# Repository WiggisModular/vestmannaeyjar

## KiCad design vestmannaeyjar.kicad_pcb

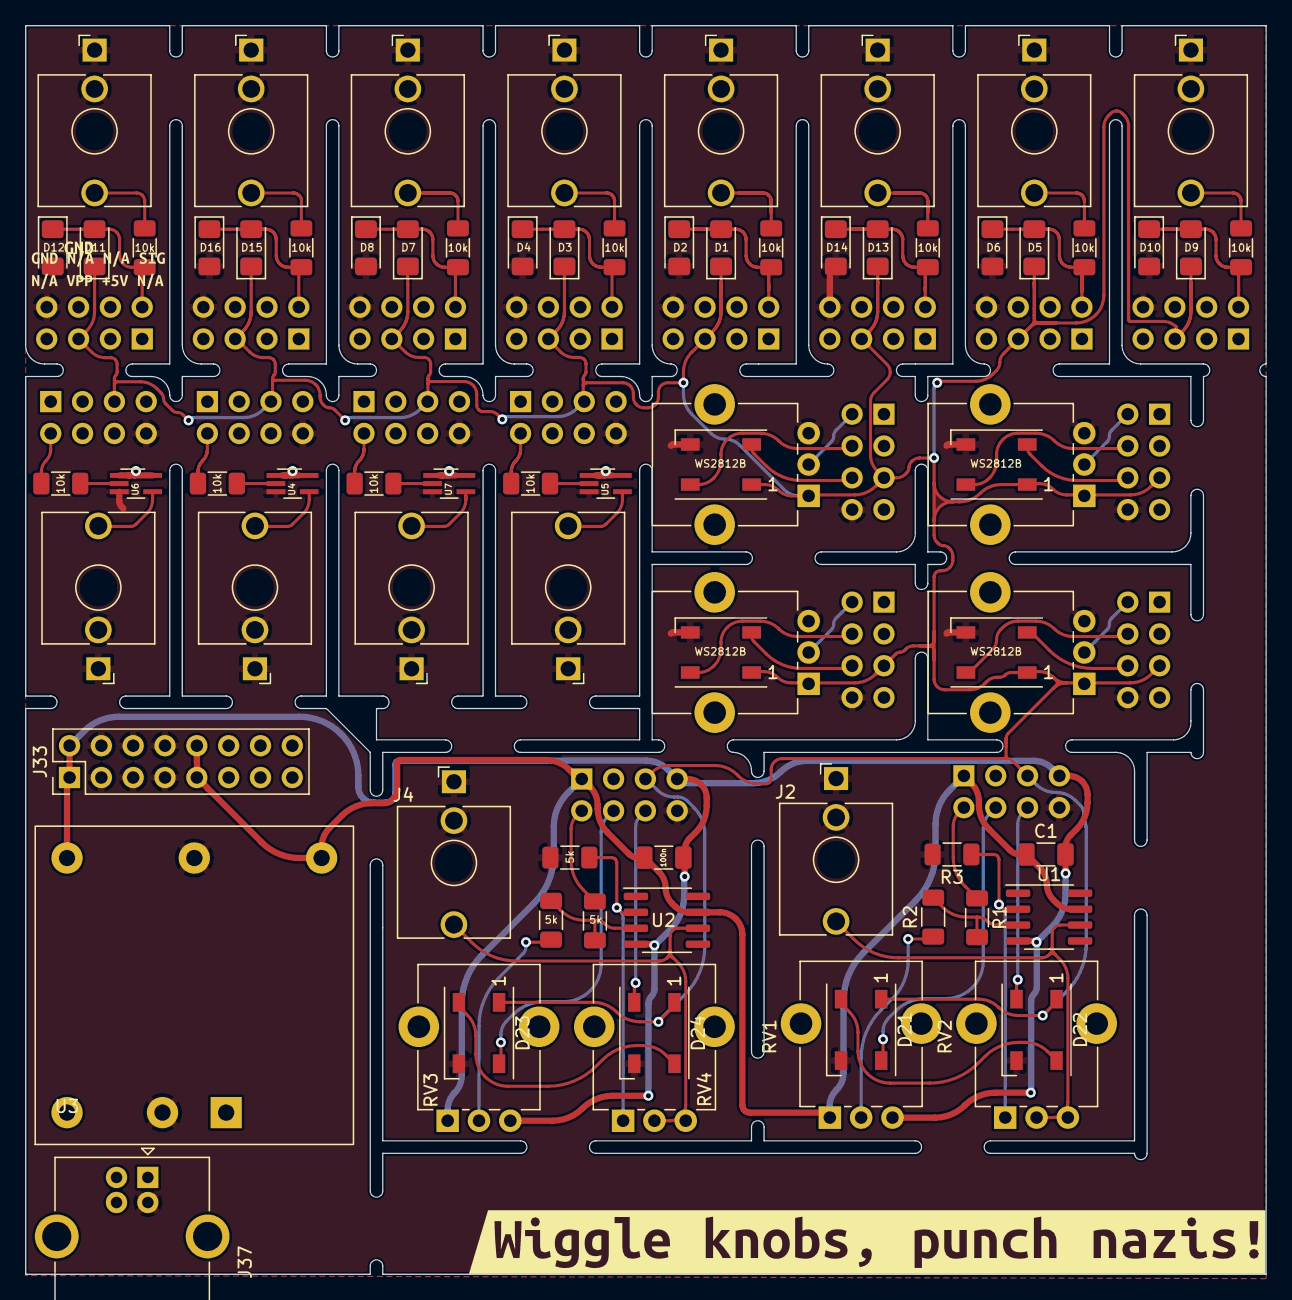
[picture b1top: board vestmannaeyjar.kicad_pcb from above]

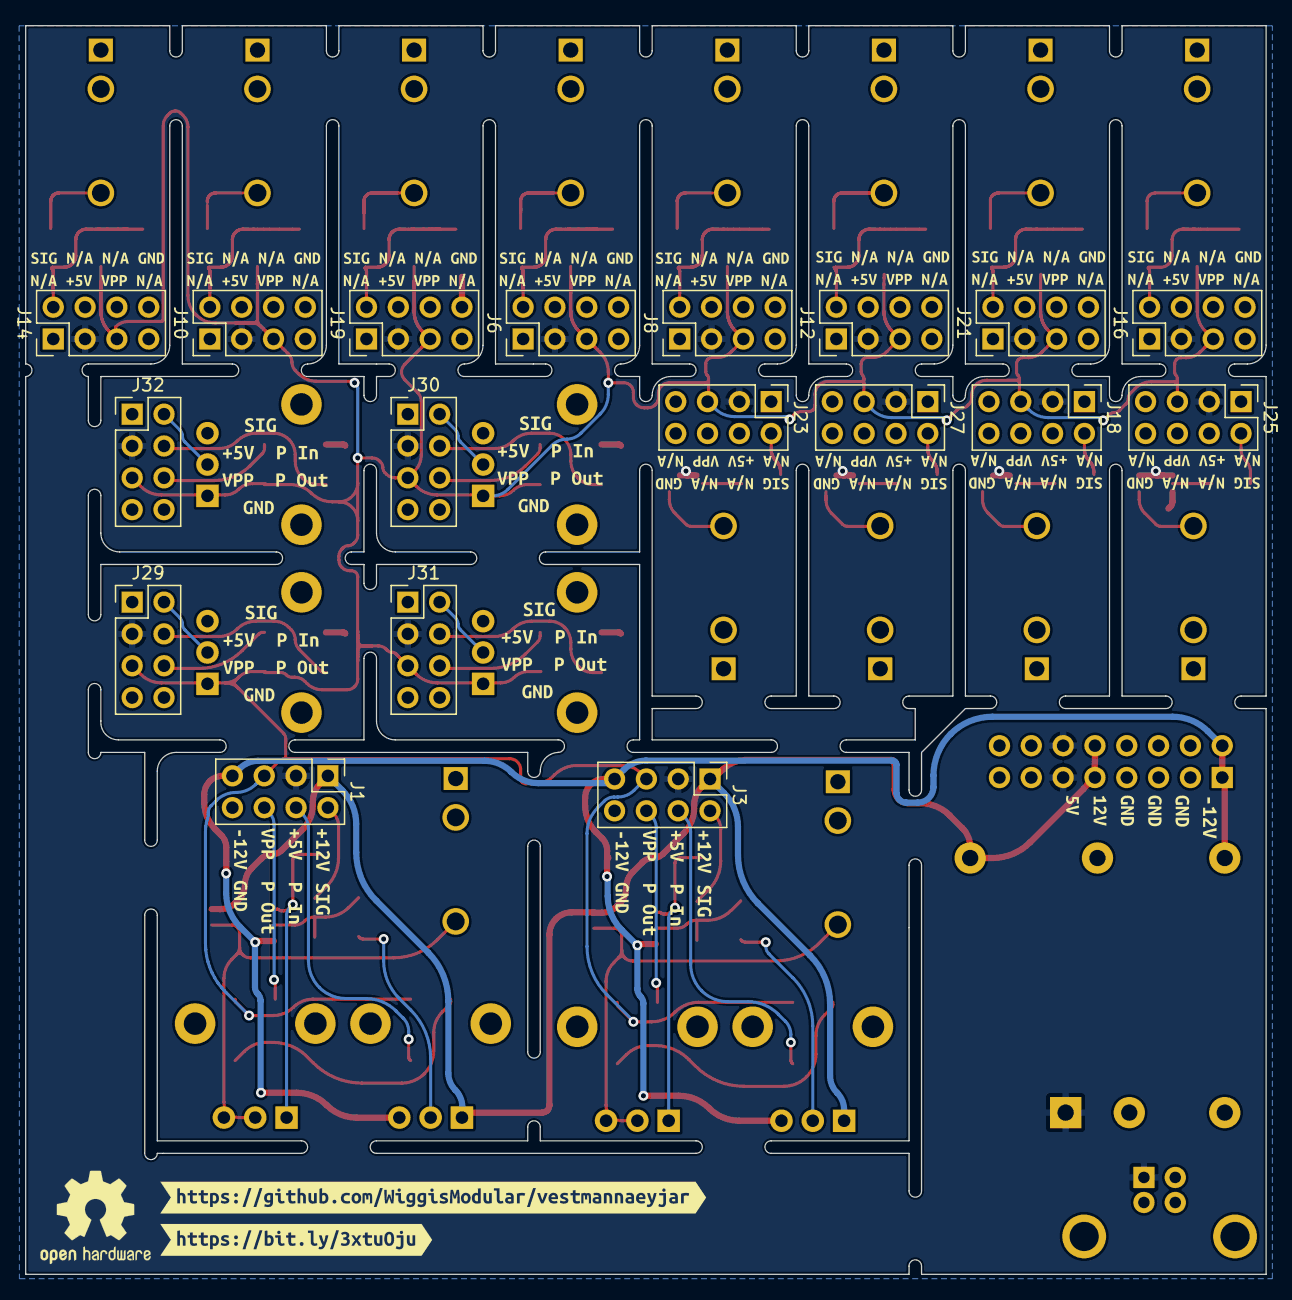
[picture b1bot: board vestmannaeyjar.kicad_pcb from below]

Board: 2 copper layers, 99.0 x 99.7 mm, 117 parts (39 on the bottom side), 61 nets.

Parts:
C1, C2: 100n; C_1206_3216Metric_Pad1.33x1.80mm_HandSolder
D1, D2, D3, D4, D5, D6, D7, D8, D9, D10, D11, D12, D13, D14, D15, D16: D; D_1206_3216Metric_Pad1.42x1.75mm_HandSolder
D17, D18, D19, D20, D21, D22, D23, D24: WS2812B; LED_WS2812B_PLCC4_5.0x5.0mm_P3.2mm
J1, J3, J6, J8, J10, J12, J14, J16, J18, J19, J21, J23, J25, J27, J29, J30, J31, J32: Conn_02x04_Odd_Even; PinHeader_2x04_P2.54mm_Vertical
J2, J4, J5, J7, J9, J11, J13, J15, J17, J20, J22, J24, J26, J28: AudioJack2_SwitchT; Jack_3.5mm_QingPu_WQP-PJ398SM_Vertical_CircularHoles
J33: Conn_02x08_Odd_Even; PinHeader_2x08_P2.54mm_Vertical
J37: USB_B; USB_B_OST_USB-B1HSxx_Horizontal
R1, R2, R3, R4, R5, R6: 5k; R_1206_3216Metric_Pad1.30x1.75mm_HandSolder
R7, R8, R9, R10, R11, R12, R13, R14, R15, R16, R17, R18: 10k; R_1206_3216Metric_Pad1.30x1.75mm_HandSolder
RV1, RV2, RV3, RV4, RV5, RV6, RV7, RV8: R_Potentiometer; Potentiometer_Alpha_RD901F-40-00D_Single_Vertical_CircularH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
U1, U2: TL071; SOIC-8_3.9x4.9mm_P1.27mm
U3: DKM10E-12; DKM10
U4, U5, U6, U7: 74AHCT1G126GV; SOT-353_SC-70-5_Handsoldering
kibuzzard-629F7A01: G***; kibuzzard-629F7A01
kibuzzard-629F76EE: G***; kibuzzard-629F76EE
kibuzzard-629F79BD, kibuzzard-629F79BD#2, kibuzzard-629F79BD#3, kibuzzard-629F79BD#4: G***; kibuzzard-629F79BD
kibuzzard-629F7599: G***; kibuzzard-629F7599
kibuzzard-629F7671: G***; kibuzzard-629F7671
kibuzzard-629F7781, kibuzzard-629F7781#2, kibuzzard-629F7781#3, kibuzzard-629F7781#4, kibuzzard-629F7781#5, kibuzzard-629F7781#6, kibuzzard-629F7781#7, kibuzzard-629F7781#8, kibuzzard-629F7781#9, kibuzzard-629F7781#10, kibuzzard-629F7781#11, kibuzzard-629F7781#12: G***; kibuzzard-629F7781
kibuzzard-629F7972, kibuzzard-629F7972#2: G***; kibuzzard-629F7972
kibuzzard-629FABBF: G***; kibuzzard-629FABBF
kibuzzard-629FAC56: G***; kibuzzard-629FAC56

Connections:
+5V: J1.3, J3.3, J6.3, J8.3, J10.3, J12.3, J14.3, J16.3, J18.3, J19.3, J21.3, J23.3, J25.3, J27.3, J29.3, J30.3, J31.3, J32.3, J33.11, J33.12, J37.1 (VBUS), U3.1 (+VIN), U4.1, U4.5 (VCC), U5.1, U5.5 (VCC), U6.1, U6.5 (VCC), U7.1, U7.5 (VCC)
+12V: C1.1, C2.1, J1.1, J3.1, J33.9, J33.10, RV1.1, RV3.1, U1.7 (V+), U2.7 (V+), U3.3 (+VOUT)
-12V: C1.2, C2.2, J1.7, J3.7, J33.1, J33.2, RV1.3, RV3.3, U1.4 (V-), U2.4 (V-), U3.5 (-VOUT)
GND: D2.2 (A), D4.2 (A), D6.2 (A), D8.2 (A), D10.2 (A), D12.2 (A), D14.2 (A), D16.2 (A), D17.3 (VSS), D18.3 (VSS), D19.3 (VSS), D20.3 (VSS), D21.3 (VSS), D22.3 (VSS), D23.3 (VSS), D24.3 (VSS), J1.8, J2.S, J2.TN, J3.8, J4.S, J4.TN, J5.S, J5.TN, J6.8, J7.S, J7.TN, J8.8, J9.S, J9.TN, J10.8, J11.S, J11.TN, J12.8, J13.S, J13.TN, J14.8, J15.S, J15.TN, J16.8, J17.S, J17.TN, J18.8, J19.8, J20.S, J20.TN, J21.8, J22.S, J22.TN, J23.8, J24.S, J24.TN, J25.8, J26.S, J26.TN, J27.8, J28.S, J28.TN, J29.8, J30.8, J31.8, J32.8, J33.3, J33.4, J33.5, J33.6, J33.7, J33.8, J37.4 (GND), R3.2, R6.2, RV5.3, RV6.3, RV7.3, RV8.3, U3.2 (-VIN), U3.4 (Common), U4.3 (GND), U5.3 (GND), U6.3 (GND), U7.3 (GND)
unnamed: D1.2 (A), D2.1 (K), J6.2, R7.2
unnamed: D3.2 (A), D4.1 (K), J8.2, R8.2
unnamed: D5.2 (A), D6.1 (K), J10.2, R9.2
unnamed: D7.2 (A), D8.1 (K), J12.2, R10.2
unnamed: D9.2 (A), D10.1 (K), J14.2, R11.2
unnamed: D11.2 (A), D12.1 (K), J16.2, R12.2
unnamed: D13.2 (A), D14.1 (K), J19.2, R13.2
unnamed: D15.2 (A), D16.1 (K), J21.2, R14.2
unnamed: D17.2 (DOUT), J29.6
unnamed: D17.4 (DIN), J29.4
unnamed: D18.2 (DOUT), J30.6
unnamed: D18.4 (DIN), J30.4
unnamed: D19.2 (DOUT), J31.6
unnamed: D19.4 (DIN), J31.4
unnamed: D20.2 (DOUT), J32.6
unnamed: D20.4 (DIN), J32.4
unnamed: D21.2 (DOUT), D22.4 (DIN)
unnamed: D21.4 (DIN), J1.4
unnamed: D22.2 (DOUT), J1.6
unnamed: D23.2 (DOUT), D24.4 (DIN)
unnamed: D23.4 (DIN), J3.4
unnamed: D24.2 (DOUT), J3.6
unnamed: J1.2, R1.1
unnamed: J2.T, RV2.2, RV2.3, U1.6
unnamed: J3.2, R4.1
unnamed: J4.T, RV4.2, RV4.3, U2.6
unnamed: J5.T, R7.1
unnamed: J7.T, R8.1
unnamed: J9.T, R9.1
unnamed: J11.T, R10.1
unnamed: J13.T, R11.1
unnamed: J15.T, R12.1
unnamed: J17.T, R13.1
unnamed: J18.2, R15.2
unnamed: J20.T, R14.1
unnamed: J22.T, U4.4
unnamed: J23.2, R16.2
unnamed: J24.T, U5.4
unnamed: J25.2, R17.2
unnamed: J26.T, U6.4
unnamed: J27.2, R18.2
unnamed: J28.T, U7.4
unnamed: J29.2, RV5.2
unnamed: J30.2, RV6.2
unnamed: J31.2, RV7.2
unnamed: J32.2, RV8.2
unnamed: R1.2, R2.2, U1.3 (+)
unnamed: R2.1, RV1.2
unnamed: R3.1, RV2.1, U1.2 (-)
unnamed: R4.2, R5.2, U2.3 (+)
unnamed: R5.1, RV3.2
unnamed: R6.1, RV4.1, U2.2 (-)
unnamed: R15.1, U4.2
unnamed: R16.1, U5.2
unnamed: R17.1, U6.2
unnamed: R18.1, U7.2
VPP: D1.1 (K), D3.1 (K), D5.1 (K), D7.1 (K), D9.1 (K), D11.1 (K), D13.1 (K), D15.1 (K), D17.1 (VDD), D18.1 (VDD), D19.1 (VDD), D20.1 (VDD), D21.1 (VDD), D22.1 (VDD), D23.1 (VDD), D24.1 (VDD), J1.5, J3.5, J6.5, J8.5, J10.5, J12.5, J14.5, J16.5, J18.5, J19.5, J21.5, J23.5, J25.5, J27.5, J29.5, J30.5, J31.5, J32.5, RV5.1, RV6.1, RV7.1, RV8.1

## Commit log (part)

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2022-06-03 manufacturing files generated
2022-06-03 trace fixed
2022-06-07 Switched to two layers
